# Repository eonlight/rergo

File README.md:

# rergo v4.0.3

Custom made keyboard using ergopad, ergogen and kicad

# V4

[rergo v4 design](/designs/v4/)

[rergo v4 kicad](/kicad/v4/)

[rergo v4 zmk config](/zmk-config/v4/)

# V3

[rergo v3 design](/designs/v3/)

[rergo v3 kicad](/kicad/v3/)

[rergo v3 zmk config](/zmk-config/v3/)

# V2

[rergo v2 design](/designs/v2/)

# V1

[rergo v1 design](/designs/v1/)

### Firmware (ZMK)

The keyboard runs [ZMK](https://zmk.dev). v4 firmware lives in its own repo (`zmk-config`); earlier versions are under [/zmk-config/v3/](/zmk-config/v3/). It builds a custom out-of-tree shield `rergo` for the **nice_nano v2**, split left/right.

* **Docker image must match ZMK's Zephyr version.** ZMK `main` pulls Zephyr 4.1, which needs Zephyr SDK 0.16/0.17 → use `zmkfirmware/zmk-build-arm:4.1-branch`. The `4.4-branch` image (SDK 1.0.1) is incompatible and will not build.
* First-time setup (fetches ~2GB into gitignored dirs): from the config repo root,
    ```
    docker run --rm -v"$(pwd)":/tmp/zmk-config -w /tmp/zmk-config zmkfirmware/zmk-build-arm:4.1-branch \
      bash -c 'west update && west zephyr-export'
    ```
* Build a target (`rergo_left` / `rergo_right` / `settings_reset`; see `build.yaml`). Run `west zephyr-export` again in the same container — it does not persist across `docker run`:
    ```
    docker run --rm -v"$(pwd)":/tmp/zmk-config -w /tmp/zmk-config zmkfirmware/zmk-build-arm:4.1-branch bash -c '
      west zephyr-export >/dev/null 2>&1
      west build -s zmk/app -d build/left -b "nice_nano//zmk" -S studio-rpc-usb-uart -- \
        -DSHIELD=rergo_left -DZMK_CONFIG=/tmp/zmk-config/config \
        -DZMK_EXTRA_MODULES=/tmp/zmk-config -DCONFIG_ZMK_STUDIO=y'
    ```
    Output is `build/<target>/zephyr/zmk.uf2`. Flash by double-tapping reset and copying the `.uf2` to the `NICENANO` USB drive.
* **Left half is central** (USB + ZMK Studio); right half is a BLE peripheral. Flash the matching `.uf2` to each.
* `settings_reset.uf2` clears stored BLE bonds — flash to both halves if pairing gets stuck, then reflash the normal firmware.

### Testing / bring-up

You do **not** need every diode and switch soldered to test a key — each key is an independent path (`col → switch → diode → row`). Test with only the nice_nano + that key's diode soldered; **bridge the switch pads with tweezers** to simulate a press.

Order of operations:
1. **Before soldering the nice_nano**: continuity-check every diode's orientation (see Diode Notes — cathode/`|` toward the row).
2. **Solder + flash the nice_nano**, then confirm the left half enumerates over USB (types characters / shows up in [ZMK Studio](https://studio.zmk.dev), enabled in this firmware).
3. **Walk the matrix**: short each key's pads with tweezers and watch the character appear in a text editor or key highlight in ZMK Studio. A key that never registers → recheck that key's diode joint and its col/row solder.
4. Only after the whole matrix reads correctly, solder the switches. Repeat for the right half (flash `rergo_right.uf2`, or pair it to the left and test via Studio).

Multimeter checks (power off):
* Use **diode mode** (not plain continuity) when a diode is in the path — `col2row` means it conducts col → row only. Red on the col pad, black on the row pad → ~0.5–0.7 V when pressed, open when released; reversed probes stay open (confirms diode direction).
* Plain continuity: switch pad ↔ its nice_nano pin pad (catches cold joints); adjacent col/row pins should **not** be connected when idle (catches bridges).
* **Use the pads on the other side of the soldered components to test things (diode/socket)**
* shorting the pads on the other side should produce a key
* **THE LIKELY PROBLEM IS THE DIODE!!!!**

Deeper firmware debugging: add `CONFIG_ZMK_USB_LOGGING=y` to `config/rergo.conf`, rebuild, and open the USB serial port to see raw key press/release events with position numbers (turn it off for daily use — it raises power draw).

#### Chatter (one press prints multiple characters)

**Check the hotswap socket joints first — that was the cause on v4.** A socket that looks soldered but isn't fully wetted makes intermittent contact, which the firmware reads as release + re-press. Reflowing the socket fixed it. Other hardware suspects: cold joint on that key's diode, or debris/wear in the switch.

To tell hardware from timing: move the switch to another socket. If the chatter follows the switch it's the switch; if it stays with the position it's the board (socket or diode joint).

Debounce tuning masks bounce but does not fix a bad joint — only reach for it once the joints are known good, or if chatter is spread evenly across many keys. The `kscan` node's defaults are 5 ms press / 5 ms release; raising **release** targets repeats without adding keystroke latency (v4 uses `debounce-release-ms = <15>`). To experiment without touching the devicetree, put `CONFIG_ZMK_KSCAN_DEBOUNCE_RELEASE_MS=25` in `config/rergo.conf` — it overrides all kscan instances. Above ~30 ms rapid double-taps start getting swallowed.

#### Firmware gotchas hit during v4 bring-up

* **No key on either half registers, but the board flashes, boots and pairs fine** → the shield is missing `chosen { zmk,kscan = &kscan0; };`. Defining the matrix node is not enough; without the `chosen` entry ZMK builds cleanly with no key scanner at all and warns about nothing.
* Every keymap layer must have **exactly one binding per key position** (46 on v4). A miscount produces only an "excess elements in array initializer" warning at build time, but silently shifts every following key on that layer.

### KiCad Notes

`x` to start routing

`v` to create via when routing

`Round Tracks` plugin to round traces (**some traces might require deleting and redoing and re applying the plugin**)

`Edit > Edit Teardrops > Apply` to create teardrops on vias (**might also require some re doing of tracks and re applying of teardrop**)

`ctr + tab` changes the views (back vs. front layers)

### Soldering notes

* remember to bridge the pads under the nice-nano with solder
* connections can be checked with a multi-meter to verify pads have been soldered properly
* battery connector pads also need to be bridged, but these will be on the other side of the board

#### Diode Notes

POS ->|- GND

- Ground should face where the `|` is
- Measure with multimeter using continuity tool
    - Voltage will drop when direction is found
- Current diode choice will have:
    - lettering at the top (right side up) when Ground is on the left
    - lettering at the bottom (up side down) when Ground is on the right
    - Left Side Half: Diodes with lettering facing up
    - Right Side Half: Diode with lettering facing down
    - Diodes go at the bottom of the board

### PCB manufacturing notes

* File > Fabrication Outputs > Gerbers
* F&B: Cu, Paste, Silkscreen, Mask and Edge.Cuts
Output Folder: gerber
* Generate Drill Files... > Generate
* Plot

### Desoldering notes
- add solder to the iron
- hold the keyboard between legs
- use fingernail to press on the middle of the keyswitch whilst heating up both prongs, one after the other
- once the switch is loose, change the grip to hold the switch on both sides
- heat both prongs 1 at the time whilst wiggle switch out
- to clean switch, use solder wick
    - heat the prong next to the wick and slide the prong out of the wick
- Extra Notes
    - if prong seems stuck, add more solder
    - drop the switch as soon as it's out, it's REALLY hot, you'll get burnt

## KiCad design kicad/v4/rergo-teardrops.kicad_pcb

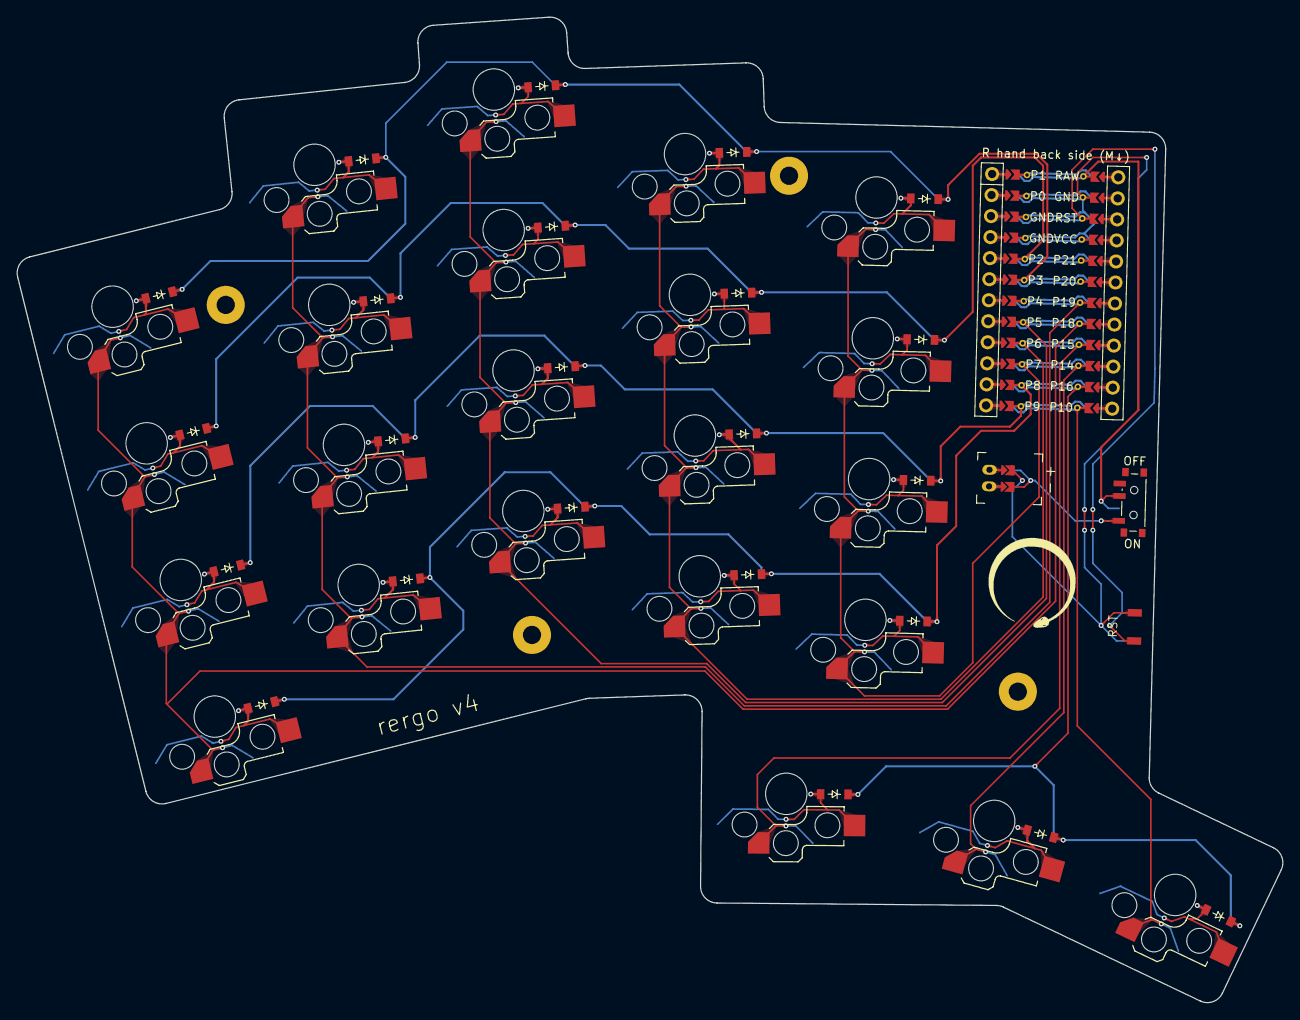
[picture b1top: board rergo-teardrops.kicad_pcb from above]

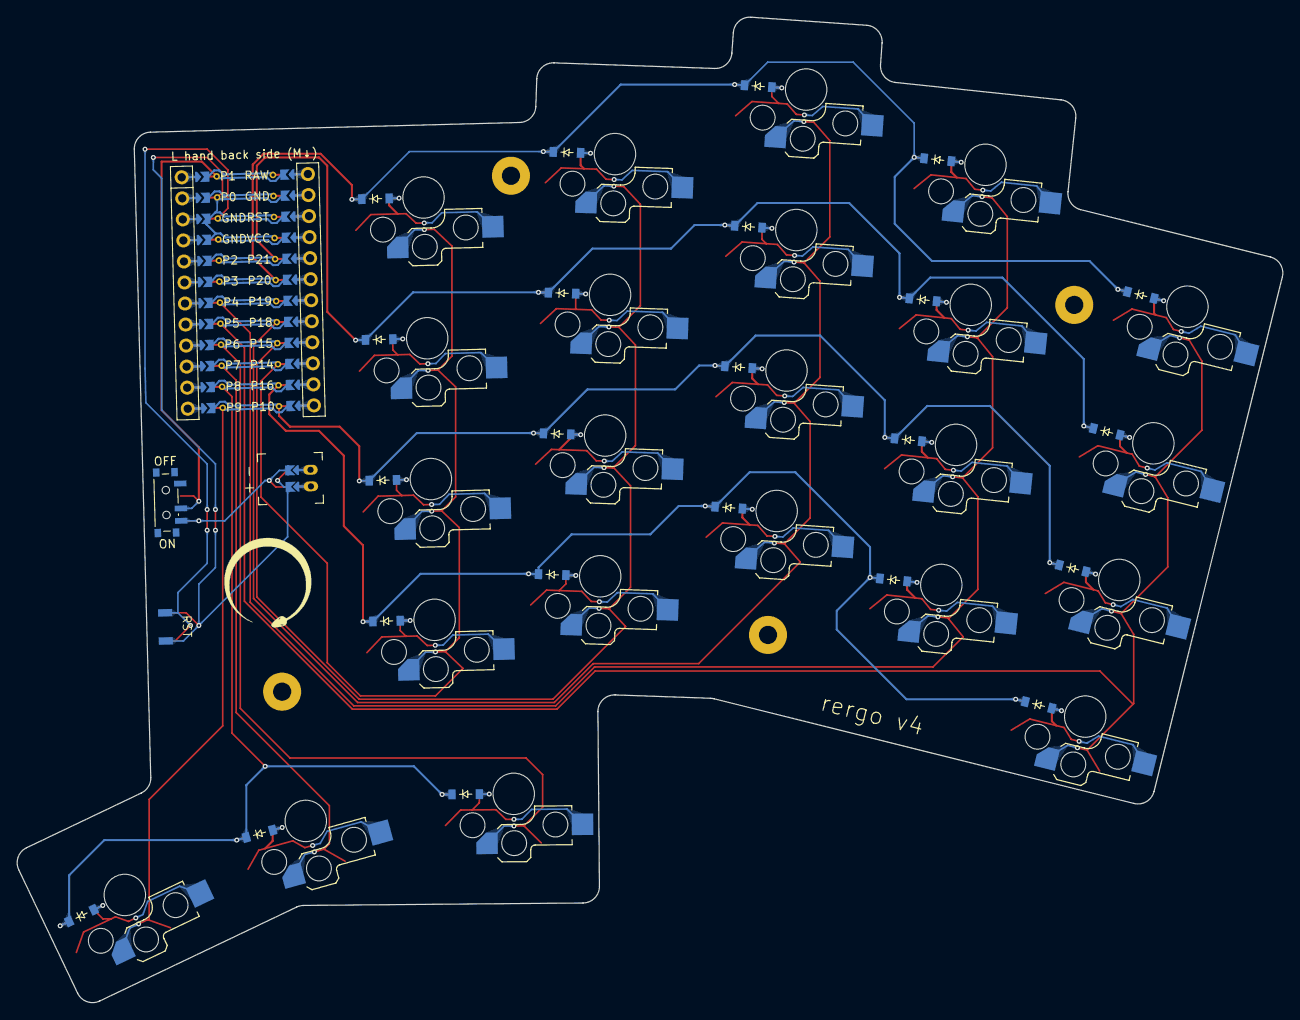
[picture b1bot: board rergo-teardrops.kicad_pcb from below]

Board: 2 copper layers, 152.8 x 119.0 mm, 55 parts (23 on the bottom side), 42 nets.

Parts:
D1, D2, D3, D4, D5, D6, D7, D8, D9, D10, D11, D12, D13, D14, D15, D16, D17, D18, D19, D20, D21, D22, D23: diode_tht_sod123
JST1: battery_connector_jst_ph_2
LOGO1: rergo logo
MCU1: mcu_nice_nano
MH1, MH2, MH3, MH4: mounting_hole_npth
PWR1: power_switch_smd_side
RST1: reset_switch_b3u_1000p
S1, S2, S3, S4, S5, S6, S7, S8, S9, S10, S11, S12, S13, S14, S15, S16, S17, S18, S19, S20, S21, S22, S23: switch_choc_v1_v2

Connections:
GND: JST1.2, MCU1.102, MCU1.121, MCU1.122, RST1.2
JST1_1: JST1.11, JST1.21, JST1.31
JST1_2: JST1.12, JST1.22, JST1.32
P2: D3.1, D7.1, D11.1, D15.1, D19.1, MCU1.120
P3: D4.1, D8.1, D12.1, D16.1, D20.1, MCU1.119
P5: MCU1.117, S9.1, S10.1, S11.1, S12.1
P6: MCU1.116, S13.1, S14.1, S15.1, S16.1
P7: MCU1.115, S17.1, S18.1, S19.1, S20.1
P8: D1.1, D5.1, D9.1, D13.1, D17.1, MCU1.114
P9: D2.1, D6.1, D10.1, D14.1, D18.1, MCU1.113
P10: MCU1.112, S23.1
P14: MCU1.110, S22.1
P15: MCU1.109, S21.1
P16: D21.1, D22.1, D23.1, MCU1.111
P18: MCU1.108, S1.1, S2.1, S3.1, S4.1
P19: MCU1.107, S5.1, S6.1, S7.1, S8.1
RAW: MCU1.101, PWR1.2
RST: MCU1.103, RST1.1
far_bottom: D17.2, S17.2
far_home: D18.2, S18.2
far_numbers: D20.2, S20.2
far_top: D19.2, S19.2
home_single: D22.2, S22.2
index_bottom: D13.2, S13.2
index_home: D14.2, S14.2
index_numbers: D16.2, S16.2
index_top: D15.2, S15.2
inner_single: D21.2, S21.2
middle_bottom: D9.2, S9.2
middle_home: D10.2, S10.2
middle_numbers: D12.2, S12.2
middle_top: D11.2, S11.2
outer_single: D23.2, S23.2
pinky_bottom: D1.2, S1.2
pinky_home: D2.2, S2.2
pinky_numbers: D4.2, S4.2
pinky_top: D3.2, S3.2
pos: JST1.1, PWR1.1, PWR1.3
ring_bottom: D5.2, S5.2
ring_home: D6.2, S6.2
ring_numbers: D8.2, S8.2
ring_top: D7.2, S7.2

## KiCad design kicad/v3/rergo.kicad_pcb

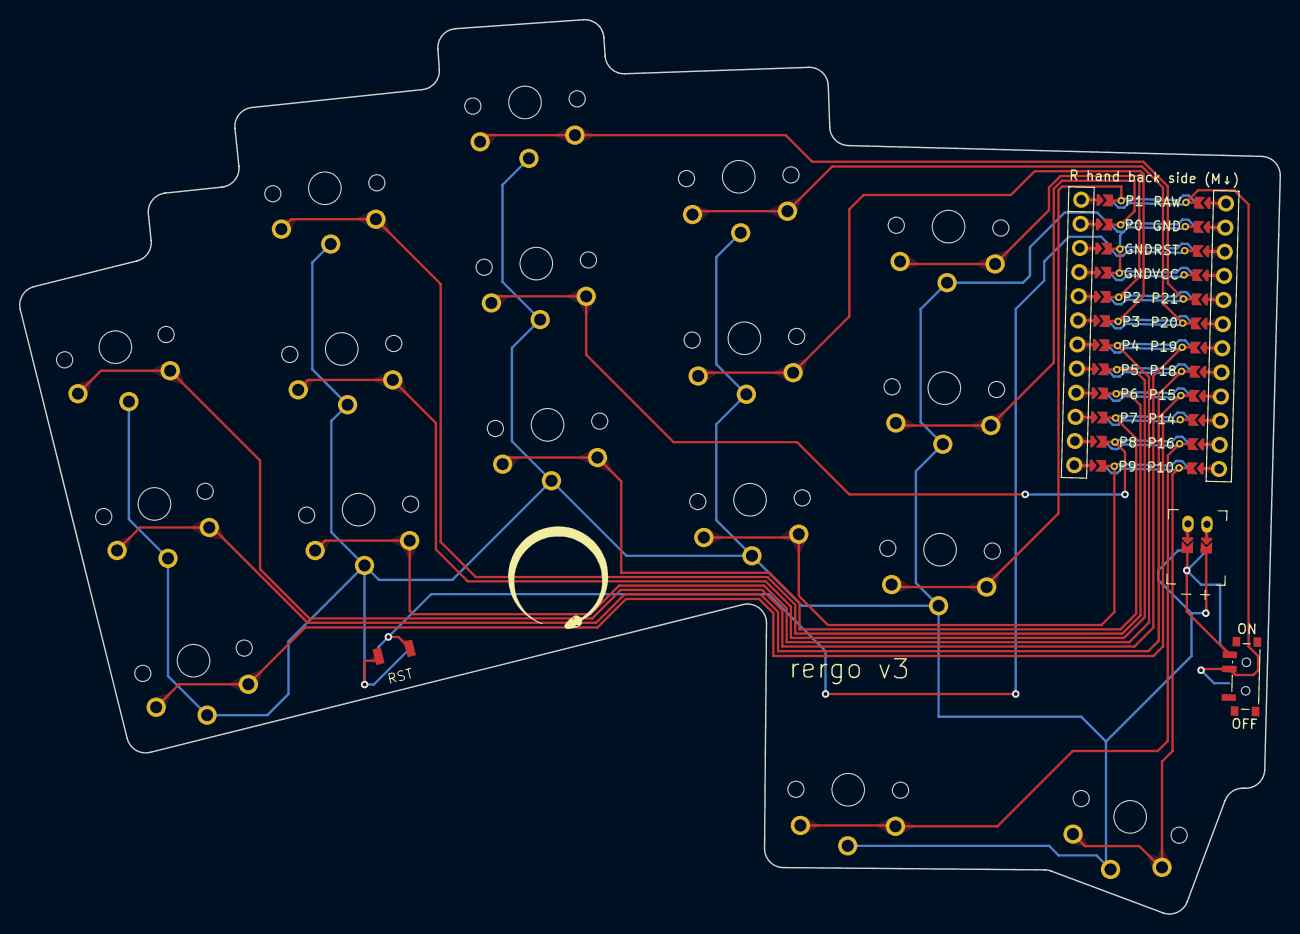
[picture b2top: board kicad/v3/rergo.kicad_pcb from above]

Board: 2 copper layers, 132.6 x 94.1 mm, 22 parts (0 on the bottom side), 23 nets.

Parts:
JST1: battery_connector_jst_ph_2
LOGO1: rergo logo
MCU1: mcu_nice_nano
PWR1: power_switch_smd_side
RST1: reset_switch_b3u_1000p
S1, S2, S3, S4, S5, S6, S7, S8, S9, S10, S11, S12, S13, S14, S15, S16, S17: PG1350

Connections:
GND: JST1.2, MCU1.102, MCU1.121, MCU1.122, RST1.2, S1.2, S2.2, S3.2, S4.2, S5.2, S6.2, S7.2, S8.2, S9.2, S10.2, S11.2, S12.2, S13.2, S14.2, S15.2, S16.2, S17.2
JST1_1: JST1.11, JST1.21, JST1.31
JST1_2: JST1.12, JST1.22, JST1.32
P0: MCU1.123, S14.1
P1: MCU1.124, S13.1
P2: MCU1.120, S15.1
P3: MCU1.119, S11.1
P4: MCU1.118, S4.1
P5: MCU1.117, S5.1
P6: MCU1.116, S6.1
P7: MCU1.115, S7.1
P8: MCU1.114, S8.1
P9: MCU1.113, S10.1
P10: MCU1.112, S17.1
P15: MCU1.109, S1.1
P16: MCU1.111, S16.1
P18: MCU1.108, S2.1
P19: MCU1.107, S3.1
P20: MCU1.106, S12.1
P21: MCU1.105, S9.1
RAW: MCU1.101, PWR1.2
RST: MCU1.103, RST1.1
pos: JST1.1, PWR1.1, PWR1.3

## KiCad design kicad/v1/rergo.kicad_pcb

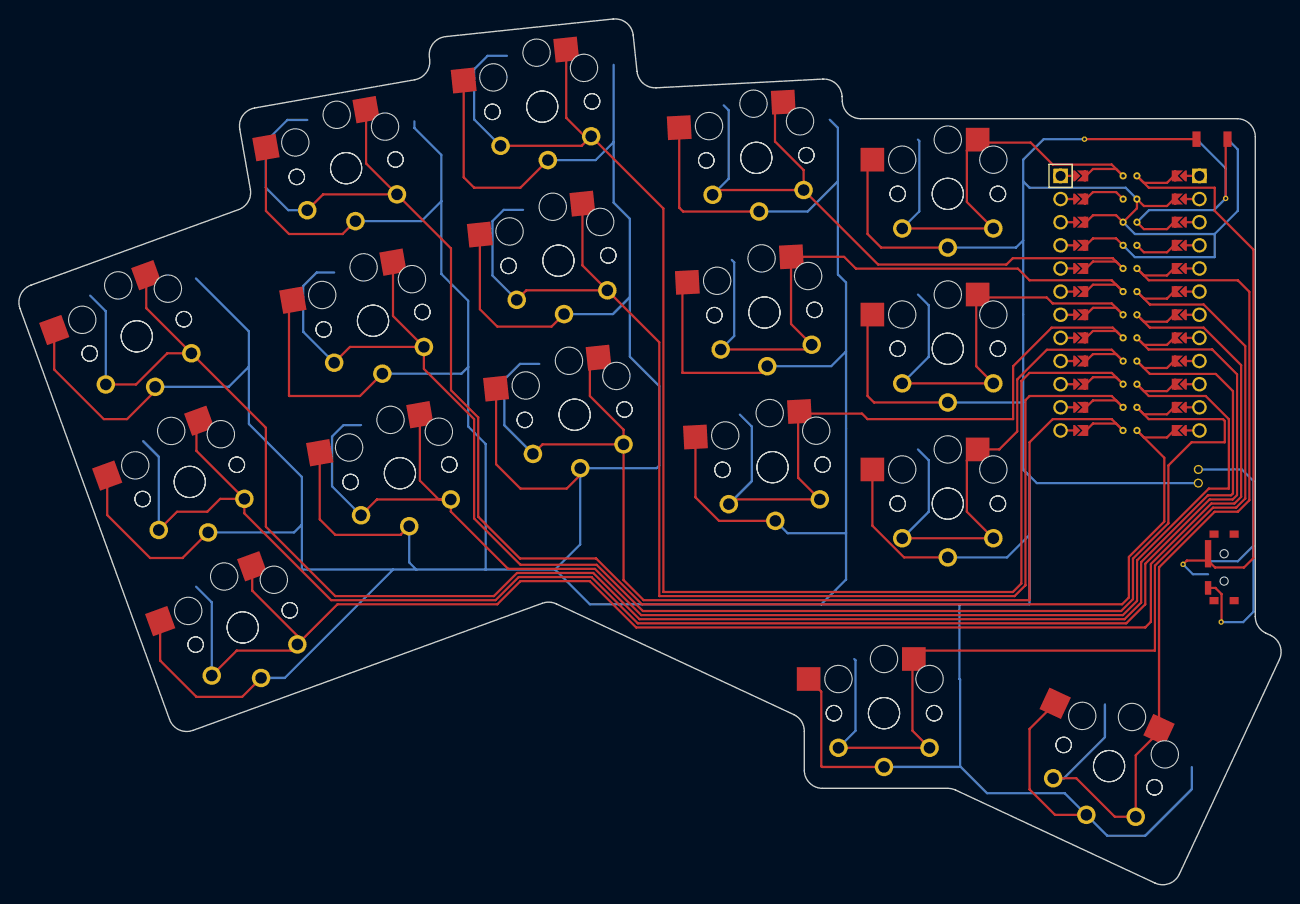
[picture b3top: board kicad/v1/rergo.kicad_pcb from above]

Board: 2 copper layers, 138.5 x 95.0 mm, 35 parts (0 on the bottom side), 18 nets.

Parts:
MCU1: ProMicro
S1, S2, S3, S4, S5, S6, S7, S8, S9, S10, S11, S12, S13, S14, S15, S16, S17, S18, S19, S20, S21, S22, S23, S24, S25, S26, S27, S28, S29, S30, S31, S32, S33, S34: PG1350

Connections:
GND: MCU1.2, MCU1.21, MCU1.22, S1.2, S2.2, S3.2, S4.2, S5.2, S6.2, S7.2, S8.2, S9.2, S10.2, S11.2, S12.2, S13.2, S14.2, S15.2, S16.2, S17.2, S18.2, S19.2, S20.2, S21.2, S22.2, S23.2, S24.2, S25.2, S26.2, S27.2, S28.2, S29.2, S30.2, S31.2, S32.2, S33.2, S34.2
P1: MCU1.24, S29.1, S30.1
P2: MCU1.20, S23.1, S24.1
P3: MCU1.19, S21.1, S22.1
P4: MCU1.18, S27.1, S28.1
P5: MCU1.17, S19.1, S20.1
P6: MCU1.16, S25.1, S26.1
P7: MCU1.15, S17.1, S18.1
P8: MCU1.14, S15.1, S16.1
P9: MCU1.13, S13.1, S14.1
P10: MCU1.12, S11.1, S12.1
P14: MCU1.10, S7.1, S8.1
P15: MCU1.9, S5.1, S6.1
P16: MCU1.11, S9.1, S10.1
P18: MCU1.8, S3.1, S4.1
P19: MCU1.7, S1.1, S2.1
P20: MCU1.6, S31.1, S32.1
P21: MCU1.5, S33.1, S34.1

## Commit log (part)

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2022-07-04 addeddesign v1 + readme
2022-07-13 added images + kicad files
2025-04-04 initial v2 commit
2025-04-06 updated design
2025-04-06 added binding, mounting holes, text, logo, kicad library for logo, better reset button footprint; removed choc hotswap; updated net points for keys
2025-04-08 updated makefile and libs
2025-04-08 added cases and kicad files
2025-04-08 removed footprints library and updated pcb image and read me
2025-04-08 updated iamges links
2025-04-12 moved tempaltes and added feet recesses to bototm plate
2025-04-12 added test version config
2025-04-12 added kicad notes
2025-04-12 Added some mroe notes
2025-04-15 added zmk-config files
2025-04-27 updated v3 no round tracks + added gerber files
2025-04-27 added v3 zmk config
2025-04-27 updated gerber files
2025-05-01 v3 zmk config
2025-05-01 added v3 to readme
